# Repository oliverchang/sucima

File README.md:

# Sucima

## What is this?

This is the code for a controller for the Amicus Basic/Advance/Professional
table tennis robots, and a PWA for interfacing with it using bluetooth.

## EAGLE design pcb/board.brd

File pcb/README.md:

This directory contains design files for the controller PCB.

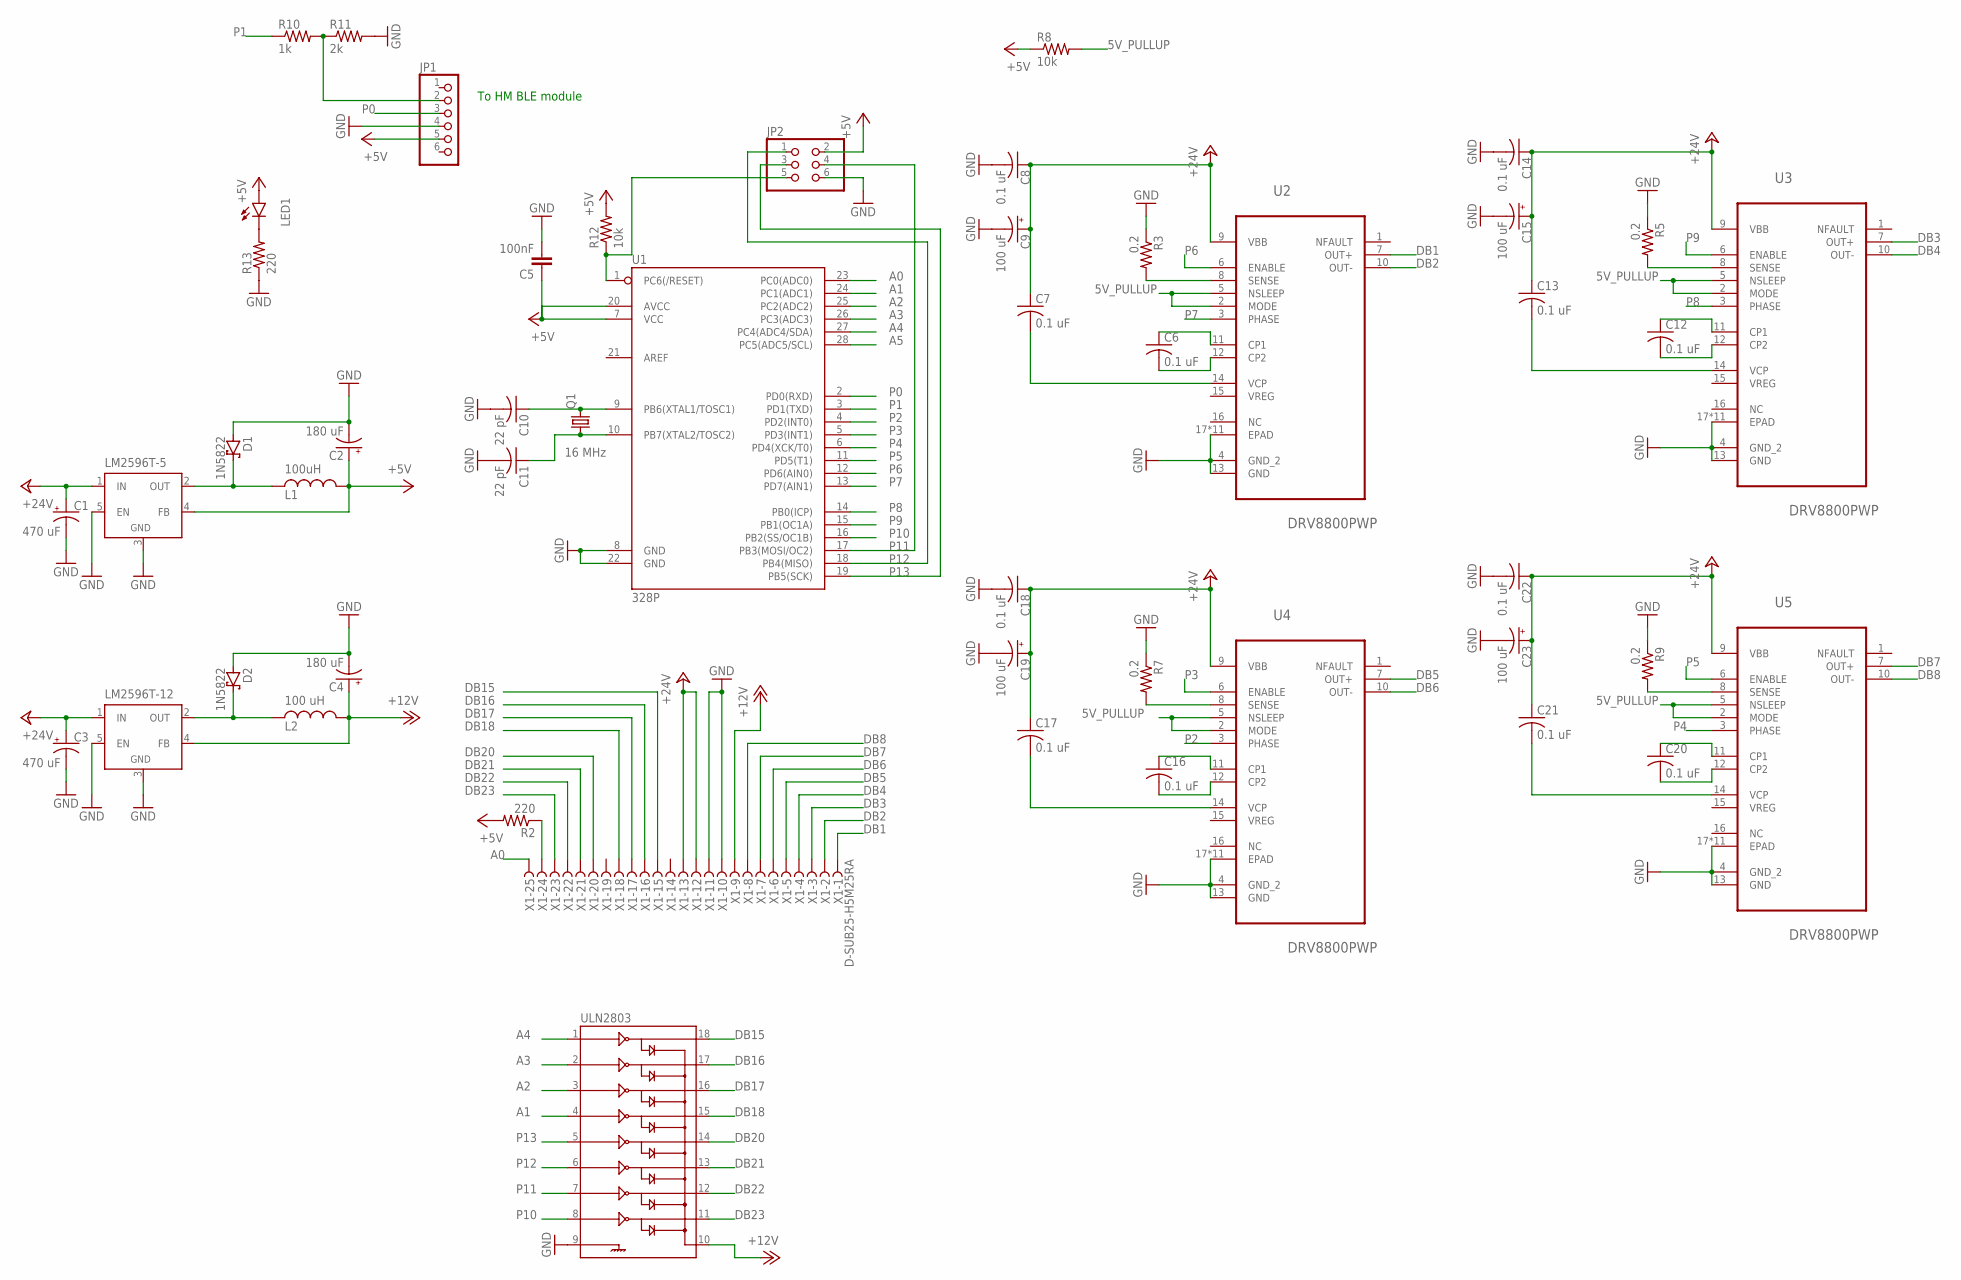
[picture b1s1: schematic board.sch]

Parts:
C1, C3: 470 uF; E3,5-8
C2, C4: 180 uF; E3,5-8
C5: 100nF; C0805
C6, C7, C8, C12, C13, C14, C16, C17, C18, C20, C21, C22: 0.1 uF; C0805
C9, C15, C19, C23: 100 uF; E3,5-8
C10, C11: 22 pF; C0805
D1, D2: 1N5822; DO201T15
JP1: PINHD-1X6; 1X06
JP2: PINHD-2X3; 2X03
L1: 100uH; SRR1260
L2: 100 uH; SRR1260
LED1: LED5MM
LM2596T-5, LM2596T-12: LM2596TV; TO220-51
Q1: 16 MHz; HC49/S
R2, R13: 220; R0805
R3, R5, R7, R9: 0.2; R0805
R8, R12: 10k; R0805
R10: 1k; R0805
R11: 2k; R0805
U1: 328P; DIP28
U2, U3, U4, U5: DRV8800PWP; SOP65P640X120-17N
ULN2803: ULN2803DIP; DIL18
X1: D-SUB25-H5M25RA; H5M25RA

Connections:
5V_PULLUP: R8.2, U2.2 (MODE), U2.5 (NSLEEP), U3.2 (MODE), U3.5 (NSLEEP), U4.2 (MODE), U4.5 (NSLEEP), U5.2 (MODE), U5.5 (NSLEEP)
+5V: C2.+, C5.1, JP1.5, JP2.2, L1.2, LED1.A, LM2596T-5.4 (FB), R2.2, R8.1, R12.2, U1.7 (VCC), U1.20 (AVCC)
+12V: C4.+, L2.2, LM2596T-12.4 (FB), ULN2803.10, X1.9
+24V: C1.+, C3.+, C7.1, C8.1, C9.+, C13.1, C14.1, C15.+, C17.1, C18.1, C19.+, C21.1, C22.1, C23.+, LM2596T-5.1 (IN), LM2596T-12.1 (IN), U2.9 (VBB), U3.9 (VBB), U4.9 (VBB), U5.9 (VBB), X1.12, X1.13
A0: U1.23 (PC0(ADC0)), X1.25
A1: U1.24 (PC1(ADC1)), ULN2803.4
A2: U1.25 (PC2(ADC2)), ULN2803.3
A3: U1.26 (PC3(ADC3)), ULN2803.2
A4: U1.27 (PC4(ADC4/SDA)), ULN2803.1
A5: U1.28 (PC5(ADC5/SCL))
DB1: U2.7 (OUT+), X1.1
DB2: U2.10 (OUT-), X1.2
DB3: U3.7 (OUT+), X1.3
DB4: U3.10 (OUT-), X1.4
DB5: U4.7 (OUT+), X1.5
DB6: U4.10 (OUT-), X1.6
DB7: U5.7 (OUT+), X1.7
DB8: U5.10 (OUT-), X1.8
DB15: ULN2803.18, X1.15
DB16: ULN2803.17, X1.16
DB17: ULN2803.16, X1.17
DB18: ULN2803.15, X1.18
DB20: ULN2803.14, X1.20
DB21: ULN2803.13, X1.21
DB22: ULN2803.12, X1.22
DB23: ULN2803.11, X1.23
GND: C1.-, C2.-, C3.-, C4.-, C5.2, C8.2, C9.-, C10.2, C11.2, C14.2, C15.-, C18.2, C19.-, C22.2, C23.-, D1.A, D2.A, JP1.4, JP2.6, LM2596T-5.3 (GND), LM2596T-5.5 (EN), LM2596T-12.3 (GND), LM2596T-12.5 (EN), R3.1, R5.1, R7.1, R9.1, R11.2, R13.1, U1.8 (GND), U1.22 (GND), U2.4 (GND_2), U2.13 (GND), U2.17 (EPAD), U2.18 (EPAD), U2.P$1 (EPAD), U2.P$2 (EPAD), U2.P$3 (EPAD), U2.P$4 (EPAD), U2.P$5 (EPAD), U2.P$6 (EPAD), U2.P$7 (EPAD), U2.P$8 (EPAD), U2.P$9 (EPAD), U3.4 (GND_2), U3.13 (GND), U3.17 (EPAD), U3.18 (EPAD), U3.P$1 (EPAD), U3.P$2 (EPAD), U3.P$3 (EPAD), U3.P$4 (EPAD), U3.P$5 (EPAD), U3.P$6 (EPAD), U3.P$7 (EPAD), U3.P$8 (EPAD), U3.P$9 (EPAD), U4.4 (GND_2), U4.13 (GND), U4.17 (EPAD), U4.18 (EPAD), U4.P$1 (EPAD), U4.P$2 (EPAD), U4.P$3 (EPAD), U4.P$4 (EPAD), U4.P$5 (EPAD), U4.P$6 (EPAD), U4.P$7 (EPAD), U4.P$8 (EPAD), U4.P$9 (EPAD), U5.4 (GND_2), U5.13 (GND), U5.17 (EPAD), U5.18 (EPAD), U5.P$1 (EPAD), U5.P$2 (EPAD), U5.P$3 (EPAD), U5.P$4 (EPAD), U5.P$5 (EPAD), U5.P$6 (EPAD), U5.P$7 (EPAD), U5.P$8 (EPAD), U5.P$9 (EPAD), ULN2803.9, X1.10, X1.11
unnamed: D1.C, L1.1, LM2596T-5.2 (OUT)
unnamed: C6.1, U2.11 (CP1)
unnamed: D2.C, L2.1, LM2596T-12.2 (OUT)
unnamed: C6.2, U2.12 (CP2)
unnamed: C7.2, U2.14 (VCP)
unnamed: R2.1, X1.24
unnamed: C10.1, Q1.2, U1.9 (PB6(XTAL1/TOSC1))
unnamed: C11.1, Q1.1, U1.10 (PB7(XTAL2/TOSC2))
unnamed: R3.2, U2.8 (SENSE)
unnamed: C12.1, U3.11 (CP1)
unnamed: C12.2, U3.12 (CP2)
unnamed: C13.2, U3.14 (VCP)
unnamed: R5.2, U3.8 (SENSE)
unnamed: C16.1, U4.11 (CP1)
unnamed: C16.2, U4.12 (CP2)
unnamed: C17.2, U4.14 (VCP)
unnamed: R7.2, U4.8 (SENSE)
unnamed: C20.1, U5.11 (CP1)
unnamed: C20.2, U5.12 (CP2)
unnamed: C21.2, U5.14 (VCP)
unnamed: R9.2, U5.8 (SENSE)
unnamed: JP1.2, R10.2, R11.1
unnamed: JP2.5, R12.1, U1.1 (PC6(/RESET))
unnamed: LED1.K (C), R13.2
P0: JP1.3, U1.2 (PD0(RXD))
P1: R10.1, U1.3 (PD1(TXD))
P2: U1.4 (PD2(INT0)), U4.3 (PHASE)
P3: U1.5 (PD3(INT1)), U4.6 (ENABLE)
P4: U1.6 (PD4(XCK/T0)), U5.3 (PHASE)
P5: U1.11 (PD5(T1)), U5.6 (ENABLE)
P6: U1.12 (PD6(AIN0)), U2.6 (ENABLE)
P7: U1.13 (PD7(AIN1)), U2.3 (PHASE)
P8: U1.14 (PB0(ICP)), U3.3 (PHASE)
P9: U1.15 (PB1(OC1A)), U3.6 (ENABLE)
P10: U1.16 (PB2(SS/OC1B)), ULN2803.8
P11: JP2.4, U1.17 (PB3(MOSI/OC2)), ULN2803.7
P12: JP2.1, U1.18 (PB4(MISO)), ULN2803.6
P13: JP2.3, U1.19 (PB5(SCK)), ULN2803.5

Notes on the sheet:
To HM BLE module

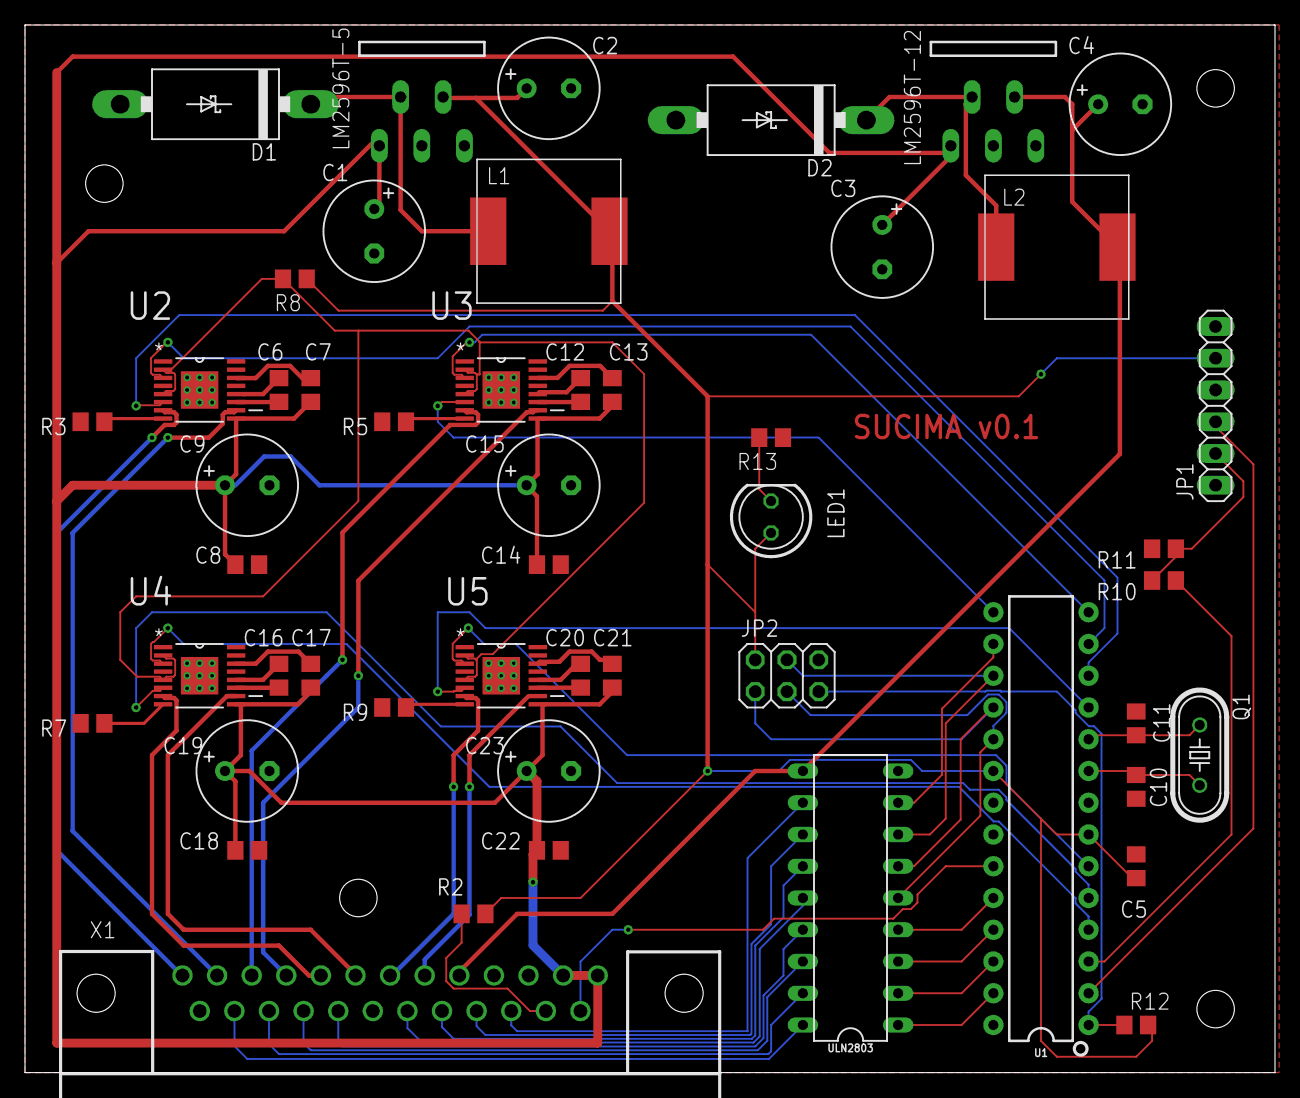
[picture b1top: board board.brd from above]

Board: 2 copper layers, 100.0 x 83.8 mm, 50 parts (0 on the bottom side), 64 nets.

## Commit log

2019-02-10 Initial commit.
2019-04-11 Publish.
2019-04-20 handle disconnection
2019-04-20 UI improvements
2019-04-20 fix exception
2019-04-20 Fixes
2019-04-29 Experimental ball jam handling.
2019-04-30 Use Vuex.
2019-04-30 connection state using vuex also.
2019-04-30 persistent state.
2019-04-30 fix some eslint issues.
2019-05-02 add reset button
2019-05-02 minor ui fixes
2019-05-30 Add case STL files.
2019-05-30 Fix typo
2019-06-01 Fix bugs in app.
    - Fix losing bluedtooth connection on loading drill.
    - Reset current ball index on reset.
2019-06-01 Upgrade packages.
2019-06-01 Fix some more bugs.
2019-06-01 add version info
2019-06-01 move install button
2019-06-01 Fix install button
2019-07-19 Fix potential race condition with command sending.
2019-07-19 update version
2019-07-19 chunk writes
2019-08-09 Add randomise functionality.
2019-08-09 fix stop button
2019-08-09 fix position range
2019-08-09 better random
2019-08-09 lower sensor threshold
2019-08-10 Adding new ball copies current ball.
2019-08-10 Change theme
2019-08-10 update style
2022-09-29 Bump @hapi/hoek and @hapi/joi in /app
    Bumps [@hapi/hoek](https://github.com/hapijs/hoek) and [@hapi/joi](https://github.com/hapijs/joi). These dependencies needed to be updated together.
    Updates `@hapi/hoek` from 6.2.4 to 8.5.1
    - [Release notes](https://github.com/hapijs/hoek/releases)
    - [Commits](https://github.com/hapijs/hoek/compare/v6.2.4...v8.5.1)
    Updates `@hapi/joi` from 15.1.0 to 15.1.1
    - [Release notes](https://github.com/hapijs/joi/releases)
2022-11-18 Bump loader-utils and @vue/cli-service in /app
    Bumps [loader-utils](https://github.com/webpack/loader-utils) to 1.4.2 and updates ancestor dependency [@vue/cli-service](https://github.com/vuejs/vue-cli/tree/HEAD/packages/@vue/cli-service). These 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
    Updates `loader-utils` from 1.2.3 to 1.4.2
    - [Release notes](https://github.com/webpack/loader-utils/releases)
    - [Changelog](https://github.com/webpack/loader-utils/blob/v1.4.2/CHANGELOG.md)
    - [Commits](https://github.com/webpack/loader-utils/compare/v1.2.3...v1.4.2)
    Updates `@vue/cli-service` from 3.10.0 to 5.0.8
2022-12-03 Bump decode-uri-component from 0.2.0 to 0.2.2 in /app
    Bumps [decode-uri-component](https://github.com/SamVerschueren/decode-uri-component) from 0.2.0 to 0.2.2.
    - [Release notes](https://github.com/SamVerschueren/decode-uri-component/releases)
    - [Commits](https://github.com/SamVerschueren/decode-uri-component/compare/v0.2.0...v0.2.2)
    ---
    updated-dependencies:
    - dependency-name: decode-uri-component
2022-12-08 Bump qs and express in /app
    Bumps [qs](https://github.com/ljharb/qs) and [express](https://github.com/expressjs/express). These dependencies needed to be updated together.
    Updates `qs` from 6.5.2 to 6.5.3
    - [Release notes](https://github.com/ljharb/qs/releases)
    - [Changelog](https://github.com/ljharb/qs/blob/main/CHANGELOG.md)
    - [Commits](https://github.com/ljharb/qs/compare/v6.5.2...v6.5.3)
    Updates `express` from 4.17.1 to 4.18.2
2022-12-10 Bump express from 4.17.1 to 4.18.2 in /app
    Bumps [express](https://github.com/expressjs/express) from 4.17.1 to 4.18.2.
    - [Release notes](https://github.com/expressjs/express/releases)
    - [Changelog](https://github.com/expressjs/express/blob/master/History.md)
    - [Commits](https://github.com/expressjs/express/compare/4.17.1...4.18.2)
    ---
    updated-dependencies:
2023-01-03 Bump json5, @vue/cli-plugin-babel and @vue/cli-service in /app
    Bumps [json5](https://github.com/json5/json5) to 2.2.3 and updates ancestor dependencies [json5](https://github.com/json5/json5), [@vue/cli-plugin-babel](https://github.com/vuejs/vue-cli/tree/HEAD/pa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
    Updates `json5` from 1.0.1 to 2.2.3
    - [Release notes](https://github.com/json5/json5/releases)
    - [Changelog](https://github.com/json5/json5/blob/main/CHANGELOG.md)
    - [Commits](https://github.com/json5/json5/compare/v1.0.1...v2.2.3)
    Updates `@vue/cli-plugin-babel`

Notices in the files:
parts and their libraries:
SparkFun-IC-Microcontroller: Licensing: Creative Commons ShareAlike 4.0 International - https://creativecommons.org/licenses/by-sa/4.0
